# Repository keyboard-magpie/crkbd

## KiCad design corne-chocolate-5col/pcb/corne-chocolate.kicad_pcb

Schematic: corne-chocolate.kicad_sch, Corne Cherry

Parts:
D2, D3, D4, D5, D6, D8, D9, D10, D11, D12, D14, D15, D16, D17, D18, D19, D20, D21, D23, D24, D25, D26, D27, D29, D30, D31, D32, D33, D35, D36, D37, D38, D39, D40, D41, D42: D; D3_SMD_v2
J1, J3: MJ-4PP-9; MJ-4PP-9_1side
J2, J4: OLED; OLED_1side
LED1, LED2, LED3, LED4, LED5, LED6, LED28, LED29, LED30, LED31, LED32, LED33: WS2812B; LED_WS2812B_PLCC4_5.0x5.0mm_P3.2mm
LED8, LED9, LED10, LED11, LED12, LED14, LED15, LED16, LED17, LED18, LED20, LED21, LED22, LED23, LED24, LED25, LED26, LED27, LED35, LED36, LED37, LED38, LED39, LED41, LED42, LED43, LED44, LED45, LED47, LED48, LED49, LED50, LED51, LED52, LED53, LED54: YS-SK6812MINI-E
RSW1, RSW2: SW_PUSH; ResetSW_1side
SW2, SW3, SW4, SW5, SW6, SW8, SW9, SW10, SW11, SW12, SW14, SW15, SW16, SW17, SW18, SW19, SW20, SW23, SW24, SW25, SW26, SW27, SW29, SW30, SW31, SW32, SW33, SW35, SW36, SW37, SW38, SW39, SW40, SW41: SW_PUSH; CherryMX_Hotswap
SW21, SW42: SW_PUSH; CherryMX_Hotswap_1.5u
U1, U2: ProMicro; ProMicro_v2_1side

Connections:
GND: J1.C, J2.4, LED1.3 (VSS), LED2.3 (VSS), LED3.3 (VSS), LED4.3 (VSS), LED5.3 (VSS), LED6.3 (VSS), LED8.3, LED9.3, LED10.3, LED11.3, LED12.3, LED14.3, LED15.3, LED16.3, LED17.3, LED18.3, LED20.3, LED21.3, LED22.3, LED23.3, LED24.3, LED25.3, LED26.3, LED27.3, RSW1.2, U1.3, U1.4, U1.23
GNDA: J3.C, J4.1, LED28.3 (VSS), LED29.3 (VSS), LED30.3 (VSS), LED31.3 (VSS), LED32.3 (VSS), LED33.3 (VSS), LED35.3, LED36.3, LED37.3, LED38.3, LED39.3, LED41.3, LED42.3, LED43.3, LED44.3, LED45.3, LED47.3, LED48.3, LED49.3, LED50.3, LED51.3, LED52.3, LED53.3, LED54.3, RSW2.2, U2.3, U2.4, U2.23
LED: LED3.4 (DIN), U1.1
LED_r: LED30.4 (DIN), U2.1
unnamed: D2.2 (A), SW2.2
unnamed: D3.2 (A), SW3.2
unnamed: D4.2 (A), SW4.2
unnamed: D5.2 (A), SW5.2
unnamed: D6.2 (A), SW6.2
unnamed: D8.2 (A), SW8.2
unnamed: D9.2 (A), SW9.2
unnamed: D10.2 (A), SW10.2
unnamed: D11.2 (A), SW11.2
unnamed: D12.2 (A), SW12.2
unnamed: D14.2 (A), SW14.2
unnamed: D15.2 (A), SW15.2
unnamed: D16.2 (A), SW16.2
unnamed: D17.2 (A), SW17.2
unnamed: D18.2 (A), SW18.2
unnamed: D19.2 (A), SW19.2
unnamed: D20.2 (A), SW20.2
unnamed: D21.2 (A), SW21.2
unnamed: D23.2 (A), SW23.2
unnamed: D24.2 (A), SW24.2
unnamed: D25.2 (A), SW25.2
unnamed: D26.2 (A), SW26.2
unnamed: D27.2 (A), SW27.2
unnamed: D29.2 (A), SW29.2
unnamed: D30.2 (A), SW30.2
unnamed: D31.2 (A), SW31.2
unnamed: D32.2 (A), SW32.2
unnamed: D33.2 (A), SW33.2
unnamed: D35.2 (A), SW35.2
unnamed: D36.2 (A), SW36.2
unnamed: D37.2 (A), SW37.2
unnamed: D38.2 (A), SW38.2
unnamed: D39.2 (A), SW39.2
unnamed: D40.2 (A), SW40.2
unnamed: D41.2 (A), SW41.2
unnamed: D42.2 (A), SW42.2
unnamed: LED1.2 (DOUT), LED4.4 (DIN)
unnamed: LED1.4 (DIN), LED2.2 (DOUT)
unnamed: LED2.4 (DIN), LED3.2 (DOUT)
unnamed: LED4.2 (DOUT), LED5.4 (DIN)
unnamed: LED5.2 (DOUT), LED6.4 (DIN)
unnamed: LED9.4, LED10.2
unnamed: LED10.4, LED16.2
unnamed: LED11.2, LED17.4
unnamed: LED11.4, LED12.2
unnamed: LED12.4, LED18.2
unnamed: LED8.4, LED14.2
unnamed: LED14.4, LED20.2
unnamed: LED15.2, LED21.4
unnamed: LED9.2, LED15.4
unnamed: LED16.4, LED22.2
unnamed: LED17.2, LED23.4
unnamed: LED18.4, LED24.2
unnamed: LED20.4, LED21.2
unnamed: LED22.4, LED25.2
unnamed: LED23.2, LED26.4
unnamed: LED24.4, LED27.2
unnamed: LED25.4, LED26.2
unnamed: LED6.2 (DOUT), LED27.4
unnamed: LED28.2 (DOUT), LED31.4 (DIN)
unnamed: LED28.4 (DIN), LED29.2 (DOUT)
unnamed: LED29.4 (DIN), LED30.2 (DOUT)
unnamed: LED31.2 (DOUT), LED32.4 (DIN)
unnamed: LED32.2 (DOUT), LED33.4 (DIN)
unnamed: LED33.2 (DOUT), LED54.4
unnamed: LED35.4, LED41.2
unnamed: LED36.2, LED42.4
unnamed: LED36.4, LED37.2
unnamed: LED37.4, LED43.2
unnamed: LED38.2, LED44.4
unnamed: LED38.4, LED39.2
unnamed: LED39.4, LED45.2
unnamed: LED41.4, LED47.2
unnamed: LED42.2, LED48.4
unnamed: LED43.4, LED49.2
unnamed: LED44.2, LED50.4
unnamed: LED45.4, LED51.2
unnamed: LED47.4, LED48.2
unnamed: LED49.4, LED52.2
unnamed: LED50.2, LED53.4
unnamed: LED51.4, LED54.2
unnamed: LED52.4, LED53.2
SCL: J2.2, U1.6
SCL_r: J4.3, U2.6
SDA: J2.1, U1.5
SDA_r: J4.4, U2.5
VCC: J1.D, J2.3, LED1.1 (VDD), LED2.1 (VDD), LED3.1 (VDD), LED4.1 (VDD), LED5.1 (VDD), LED6.1 (VDD), LED8.1, LED9.1, LED10.1, LED11.1, LED12.1, LED14.1, LED15.1, LED16.1, LED17.1, LED18.1, LED20.1, LED21.1, LED22.1, LED23.1, LED24.1, LED25.1, LED26.1, LED27.1, U1.21
VDD: J3.D, J4.2, LED28.1 (VDD), LED29.1 (VDD), LED30.1 (VDD), LED31.1 (VDD), LED32.1 (VDD), LED33.1 (VDD), LED35.1, LED36.1, LED37.1, LED38.1, LED39.1, LED41.1, LED42.1, LED43.1, LED44.1, LED45.1, LED47.1, LED48.1, LED49.1, LED50.1, LED51.1, LED52.1, LED53.1, LED54.1, U2.21
col0: U1.20
col0_r: U2.20
col1: SW2.1, SW8.1, SW14.1, U1.19
col1_r: SW23.1, SW29.1, SW35.1, U2.19
col2: SW3.1, SW9.1, SW15.1, U1.18
col2_r: SW24.1, SW30.1, SW36.1, U2.18
col3: SW4.1, SW10.1, SW16.1, SW19.1, U1.17
col3_r: SW25.1, SW31.1, SW37.1, SW40.1, U2.17
col4: SW5.1, SW11.1, SW17.1, SW20.1, U1.16
col4_r: SW26.1, SW32.1, SW38.1, SW41.1, U2.16
col5: SW6.1, SW12.1, SW18.1, SW21.1, U1.15
col5_r: SW27.1, SW33.1, SW39.1, SW42.1, U2.15
data: J1.B, U1.2
data_r: J3.B, U2.2
reset: RSW1.1, U1.22
reset_r: RSW2.1, U2.22
row0: D2.1 (K), D3.1 (K), D4.1 (K), D5.1 (K), D6.1 (K), U1.7
row0_r: D23.1 (K), D24.1 (K), D25.1 (K), D26.1 (K), D27.1 (K), U2.7
row1: D8.1 (K), D9.1 (K), D10.1 (K), D11.1 (K), D12.1 (K), U1.8
row1_r: D29.1 (K), D30.1 (K), D31.1 (K), D32.1 (K), D33.1 (K), U2.8
row2: D14.1 (K), D15.1 (K), D16.1 (K), D17.1 (K), D18.1 (K), U1.9
row2_r: D35.1 (K), D36.1 (K), D37.1 (K), D38.1 (K), D39.1 (K), U2.9
row3: D19.1 (K), D20.1 (K), D21.1 (K), U1.10
row3_r: D40.1 (K), D41.1 (K), D42.1 (K), U2.10

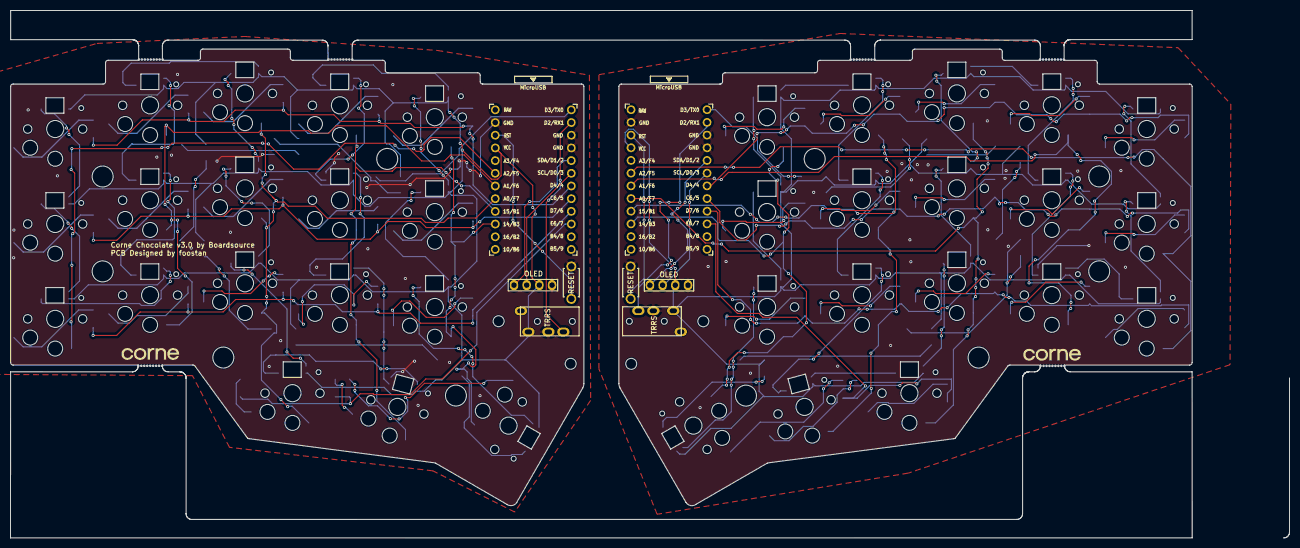
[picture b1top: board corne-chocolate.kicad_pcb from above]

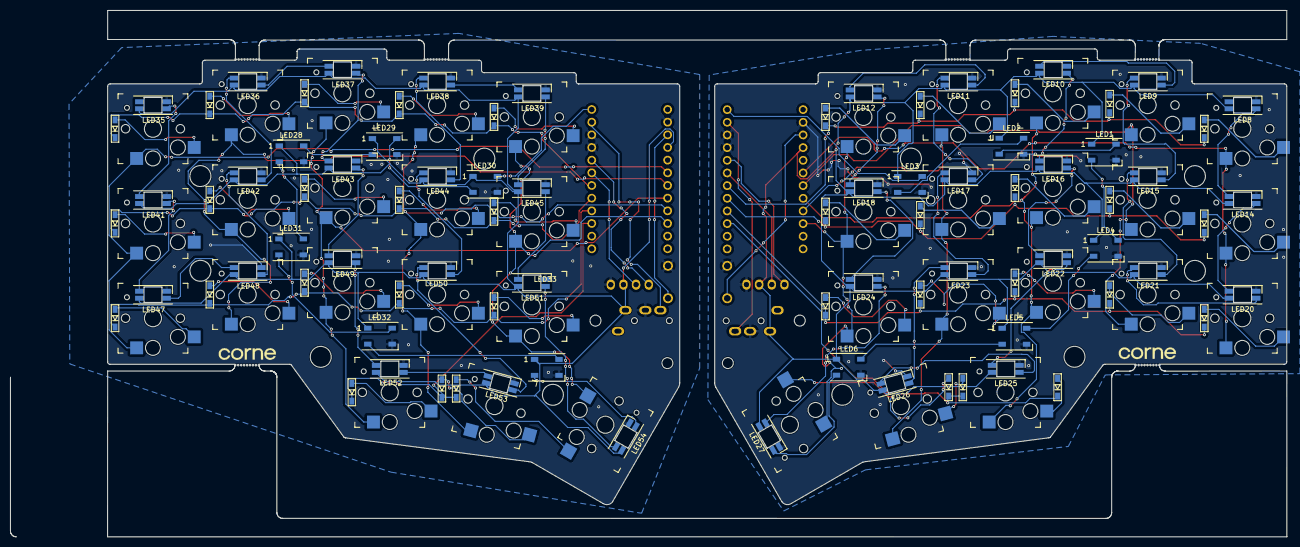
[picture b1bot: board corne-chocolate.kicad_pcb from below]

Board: 2 copper layers, 256.0 x 105.6 mm, 142 parts (91 on the bottom side), 114 nets.

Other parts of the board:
Ref**: Val**; M2_HOLE_v2
Ref**#2, Ref**#3, Ref**#4, Ref**#5, Ref**#6, Ref**#7, Ref**#8, Ref**#9, Ref**#10, Ref**#11, Ref**#12, Ref**#13, Ref**#14: Val**; M2_HOLE_v2

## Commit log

2023-02-24 add 5col corne cherry variant
2023-02-24 minor fixes to 5col
2023-02-25 corne chocolate v3 5col
2023-02-25 update corne choc v3 5col, add unrouted version for the neater people
